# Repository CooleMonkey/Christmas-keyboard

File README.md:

# Christmas-keyboard
I will tell you something about my project. As the title already says, it's a christmas themed keyboard. I made the size 60/65% and I added a numpad to the left cause I hate it when the numpad to the right is in the way of my mouse.
So that's also the first reason why I made this project. The second reason is that I wanted to challenge myself during my holliday, instead of speningd hours and hours gaming and I definitely challenged myself.
The third reason was the fact that the best christmas themed project shipped before monday 5 januari 2026 would get a 3d-printer. That was a great motivation for me to start this project, cause I really want a 3d-printer.

During this project I had some struggles with the PCB and the 3d-case, but eventually I got everyhting the right way I wanted it, so I'm pretty happy when I'm looking back at the time I have spent into this project.
The case is made up of 5 parts so it can be printed in a 3d printer.

## PCB

## Full 3D Model

## 3D Case

## Bottom Case R

## Bottom Case L

## Top Case R

## Top Case L1

## Top Case L2

## BOM

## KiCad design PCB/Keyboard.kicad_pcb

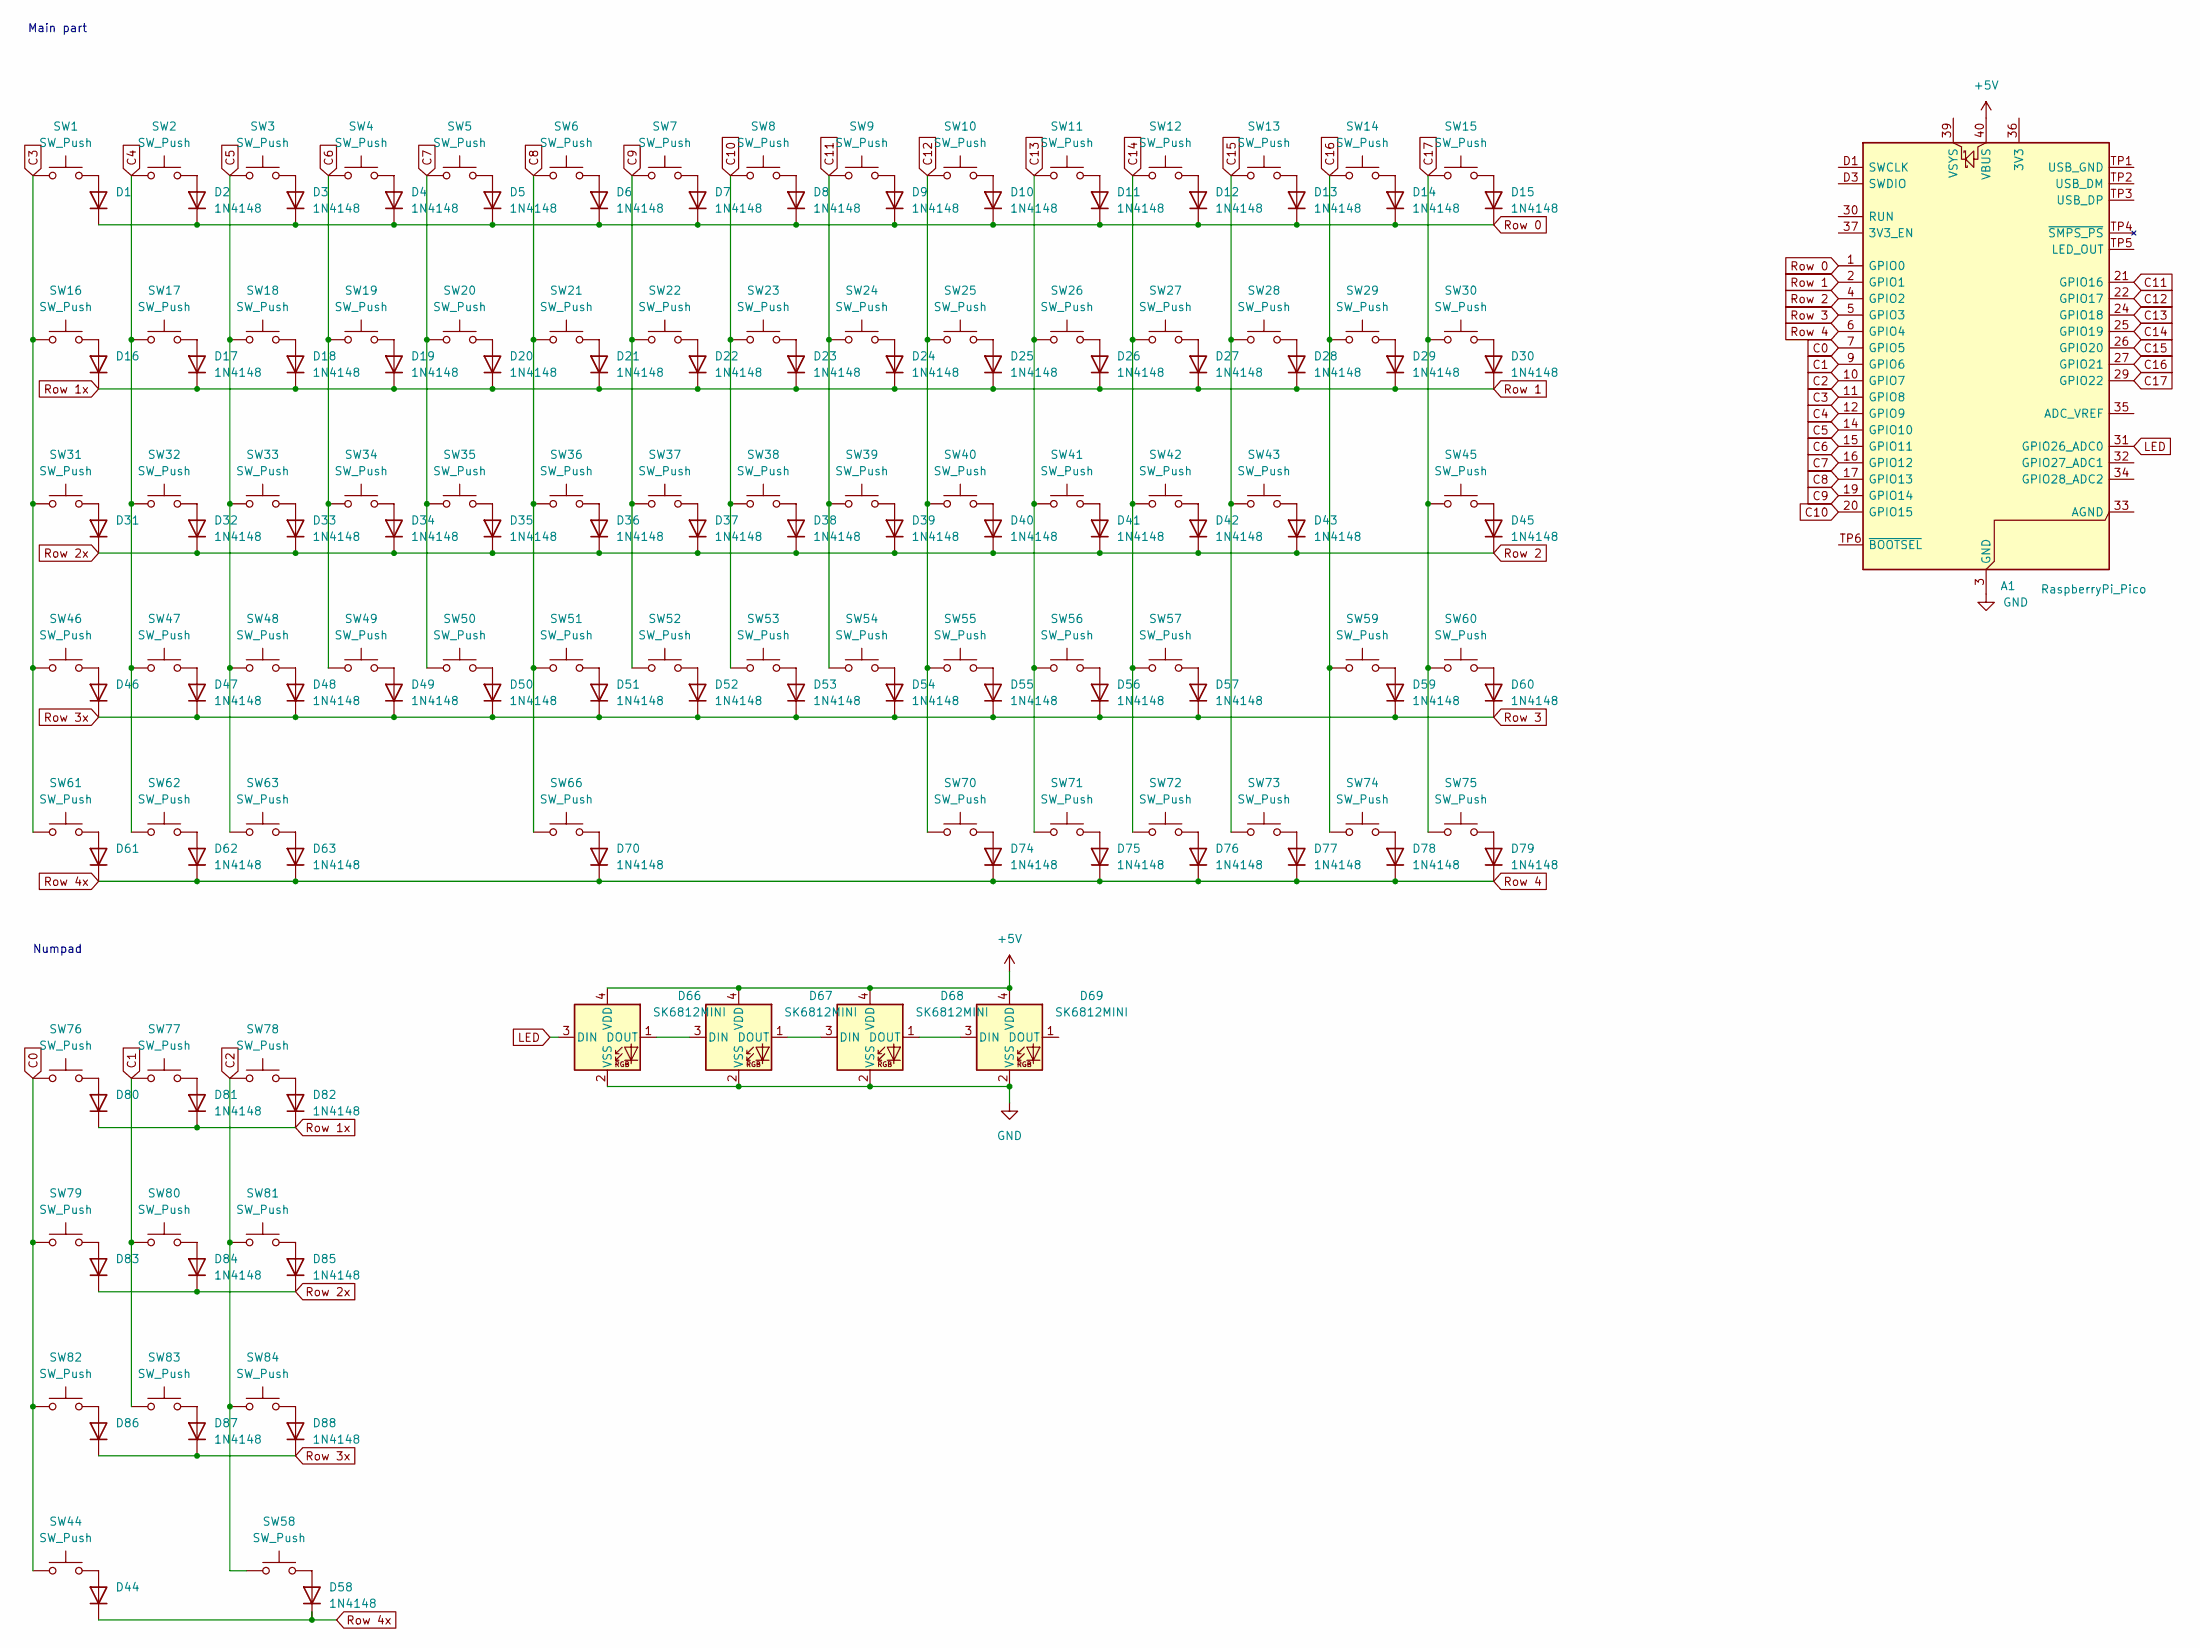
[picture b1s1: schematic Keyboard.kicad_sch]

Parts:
A1: RaspberryPi_Pico; RaspberryPi_Pico_SMD
D1, D2, D3, D4, D5, D6, D7, D8, D9, D10, D11, D12, D13, D14, D15, D16, D17, D18, D19, D20, D21, D22, D23, D24, D25, D26, D27, D28, D29, D30, D31, D32, D33, D34, D35, D36, D37, D38, D39, D40, D41, D42, D43, D44, D45, D46, D47, D48, D49, D50, D51, D52, D53, D54, D55, D56, D57, D58, D59, D60, D61, D62, D63, D70, D74, D75, D76, D77, D78, D79, D80, D81, D82, D83, D84, D85, D86, D87, D88: 1N4148; D_DO-35_SOD27_P7.62mm_Horizontal
D66, D67, D68, D69: SK6812MINI; LED_SK6812MINI_PLCC4_3.5x3.5mm_P1.75mm
SW1, SW2, SW3, SW4, SW5, SW6, SW7, SW8, SW9, SW10, SW11, SW12, SW13, SW15, SW17, SW18, SW19, SW20, SW21, SW22, SW23, SW24, SW25, SW26, SW27, SW28, SW30, SW31, SW32, SW33, SW34, SW35, SW36, SW37, SW38, SW39, SW40, SW41, SW42, SW45, SW47, SW48, SW49, SW50, SW51, SW52, SW53, SW54, SW55, SW56, SW58, SW59, SW60, SW70, SW71, SW72, SW73, SW74, SW75, SW76, SW77, SW78, SW79, SW80, SW81, SW82, SW83, SW84: SW_Push; SW_Cherry_MX_1.00u_PCB
SW14, SW44, SW46, SW57: SW_Push; SW_Cherry_MX_2.00u_PCB
SW16, SW29: SW_Push; SW_Cherry_MX_1.50u_PCB
SW43: SW_Push; SW_Cherry_MX_2.25u_PCB
SW61, SW62, SW63: SW_Push; SW_Cherry_MX_1.25u_PCB
SW66: SW_Push; SW_Cherry_MX_6.25u_PCB

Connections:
+5V: A1.40 (VBUS), D66.4 (VDD), D67.4 (VDD), D68.4 (VDD), D69.4 (VDD)
C0: A1.7 (GPIO5), SW44.1, SW76.1, SW79.1, SW82.1
C1: A1.9 (GPIO6), SW77.1, SW80.1, SW83.1
C2: A1.10 (GPIO7), SW58.1, SW78.1, SW81.1, SW84.1
C3: A1.11 (GPIO8), SW1.1, SW16.1, SW31.1, SW46.1, SW61.1
C4: A1.12 (GPIO9), SW2.1, SW17.1, SW32.1, SW47.1, SW62.1
C5: A1.14 (GPIO10), SW3.1, SW18.1, SW33.1, SW48.1, SW63.1
C6: A1.15 (GPIO11), SW4.1, SW19.1, SW34.1, SW49.1
C7: A1.16 (GPIO12), SW5.1, SW20.1, SW35.1, SW50.1
C8: A1.17 (GPIO13), SW6.1, SW21.1, SW36.1, SW51.1, SW66.1
C9: A1.19 (GPIO14), SW7.1, SW22.1, SW37.1, SW52.1
C10: A1.20 (GPIO15), SW8.1, SW23.1, SW38.1, SW53.1
C11: A1.21 (GPIO16), SW9.1, SW24.1, SW39.1, SW54.1
C12: A1.22 (GPIO17), SW10.1, SW25.1, SW40.1, SW55.1, SW70.1
C13: A1.24 (GPIO18), SW11.1, SW26.1, SW41.1, SW56.1, SW71.1
C14: A1.25 (GPIO19), SW12.1, SW27.1, SW42.1, SW57.1, SW72.1
C15: A1.26 (GPIO20), SW13.1, SW28.1, SW43.1, SW73.1
C16: A1.27 (GPIO21), SW14.1, SW29.1, SW59.1, SW74.1
C17: A1.29 (GPIO22), SW15.1, SW30.1, SW45.1, SW60.1, SW75.1
GND: A1.3 (GND), A1.8 (GND), A1.13 (GND), A1.18 (GND), A1.23 (GND), A1.28 (GND), A1.38 (GND), A1.D2 (GND), D66.2 (VSS), D67.2 (VSS), D68.2 (VSS), D69.2 (VSS)
LED: A1.31 (GPIO26_ADC0), D66.3 (DIN)
unnamed: D1.2 (A), SW1.2
unnamed: D2.2 (A), SW2.2
unnamed: D3.2 (A), SW3.2
unnamed: D4.2 (A), SW4.2
unnamed: D5.2 (A), SW5.2
unnamed: D6.2 (A), SW6.2
unnamed: D7.2 (A), SW7.2
unnamed: D8.2 (A), SW8.2
unnamed: D9.2 (A), SW9.2
unnamed: D10.2 (A), SW10.2
unnamed: D11.2 (A), SW11.2
unnamed: D12.2 (A), SW12.2
unnamed: D13.2 (A), SW13.2
unnamed: D14.2 (A), SW14.2
unnamed: D15.2 (A), SW15.2
unnamed: D16.2 (A), SW16.2
unnamed: D17.2 (A), SW17.2
unnamed: D18.2 (A), SW18.2
unnamed: D19.2 (A), SW19.2
unnamed: D20.2 (A), SW20.2
unnamed: D21.2 (A), SW21.2
unnamed: D22.2 (A), SW22.2
unnamed: D23.2 (A), SW23.2
unnamed: D24.2 (A), SW24.2
unnamed: D25.2 (A), SW25.2
unnamed: D26.2 (A), SW26.2
unnamed: D27.2 (A), SW27.2
unnamed: D28.2 (A), SW28.2
unnamed: D29.2 (A), SW29.2
unnamed: D30.2 (A), SW30.2
unnamed: D31.2 (A), SW31.2
unnamed: D32.2 (A), SW32.2
unnamed: D33.2 (A), SW33.2
unnamed: D34.2 (A), SW34.2
unnamed: D35.2 (A), SW35.2
unnamed: D36.2 (A), SW36.2
unnamed: D37.2 (A), SW37.2
unnamed: D38.2 (A), SW38.2
unnamed: D39.2 (A), SW39.2
unnamed: D40.2 (A), SW40.2
unnamed: D41.2 (A), SW41.2
unnamed: D42.2 (A), SW42.2
unnamed: D43.2 (A), SW43.2
unnamed: D44.2 (A), SW44.2
unnamed: D45.2 (A), SW45.2
unnamed: D46.2 (A), SW46.2
unnamed: D47.2 (A), SW47.2
unnamed: D48.2 (A), SW48.2
unnamed: D49.2 (A), SW49.2
unnamed: D50.2 (A), SW50.2
unnamed: D51.2 (A), SW51.2
unnamed: D52.2 (A), SW52.2
unnamed: D53.2 (A), SW53.2
unnamed: D54.2 (A), SW54.2
unnamed: D55.2 (A), SW55.2
unnamed: D56.2 (A), SW56.2
unnamed: D57.2 (A), SW57.2
unnamed: D58.2 (A), SW58.2
unnamed: D59.2 (A), SW59.2
unnamed: D60.2 (A), SW60.2
unnamed: D61.2 (A), SW61.2
unnamed: D62.2 (A), SW62.2
unnamed: D63.2 (A), SW63.2
unnamed: D66.1 (DOUT), D67.3 (DIN)
unnamed: D67.1 (DOUT), D68.3 (DIN)
unnamed: D68.1 (DOUT), D69.3 (DIN)
unnamed: D70.2 (A), SW66.2
unnamed: D74.2 (A), SW70.2
unnamed: D75.2 (A), SW71.2
unnamed: D76.2 (A), SW72.2
unnamed: D77.2 (A), SW73.2
unnamed: D78.2 (A), SW74.2
unnamed: D79.2 (A), SW75.2
unnamed: D80.2 (A), SW76.2
unnamed: D81.2 (A), SW77.2
unnamed: D82.2 (A), SW78.2
unnamed: D83.2 (A), SW79.2
unnamed: D84.2 (A), SW80.2
unnamed: D85.2 (A), SW81.2
unnamed: D86.2 (A), SW82.2
unnamed: D87.2 (A), SW83.2
unnamed: D88.2 (A), SW84.2
Row 0: A1.1 (GPIO0), D1.1 (K), D2.1 (K), D3.1 (K), D4.1 (K), D5.1 (K), D6.1 (K), D7.1 (K), D8.1 (K), D9.1 (K), D10.1 (K), D11.1 (K), D12.1 (K), D13.1 (K), D14.1 (K), D15.1 (K)
Row 1: A1.2 (GPIO1), D16.1 (K), D17.1 (K), D18.1 (K), D19.1 (K), D20.1 (K), D21.1 (K), D22.1 (K), D23.1 (K), D24.1 (K), D25.1 (K), D26.1 (K), D27.1 (K), D28.1 (K), D29.1 (K), D30.1 (K), D80.1 (K), D81.1 (K), D82.1 (K)
Row 2: A1.4 (GPIO2), D31.1 (K), D32.1 (K), D33.1 (K), D34.1 (K), D35.1 (K), D36.1 (K), D37.1 (K), D38.1 (K), D39.1 (K), D40.1 (K), D41.1 (K), D42.1 (K), D43.1 (K), D45.1 (K), D83.1 (K), D84.1 (K), D85.1 (K)
Row 3: A1.5 (GPIO3), D46.1 (K), D47.1 (K), D48.1 (K), D49.1 (K), D50.1 (K), D51.1 (K), D52.1 (K), D53.1 (K), D54.1 (K), D55.1 (K), D56.1 (K), D57.1 (K), D59.1 (K), D60.1 (K), D86.1 (K), D87.1 (K), D88.1 (K)
Row 4: A1.6 (GPIO4), D44.1 (K), D58.1 (K), D61.1 (K), D62.1 (K), D63.1 (K), D70.1 (K), D74.1 (K), D75.1 (K), D76.1 (K), D77.1 (K), D78.1 (K), D79.1 (K)

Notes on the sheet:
Numpad
Main part

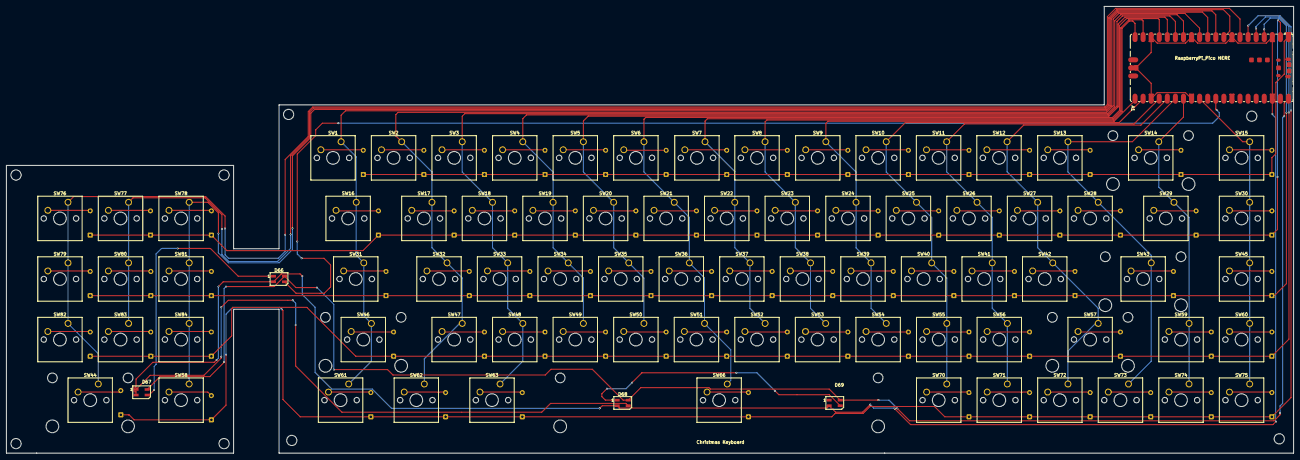
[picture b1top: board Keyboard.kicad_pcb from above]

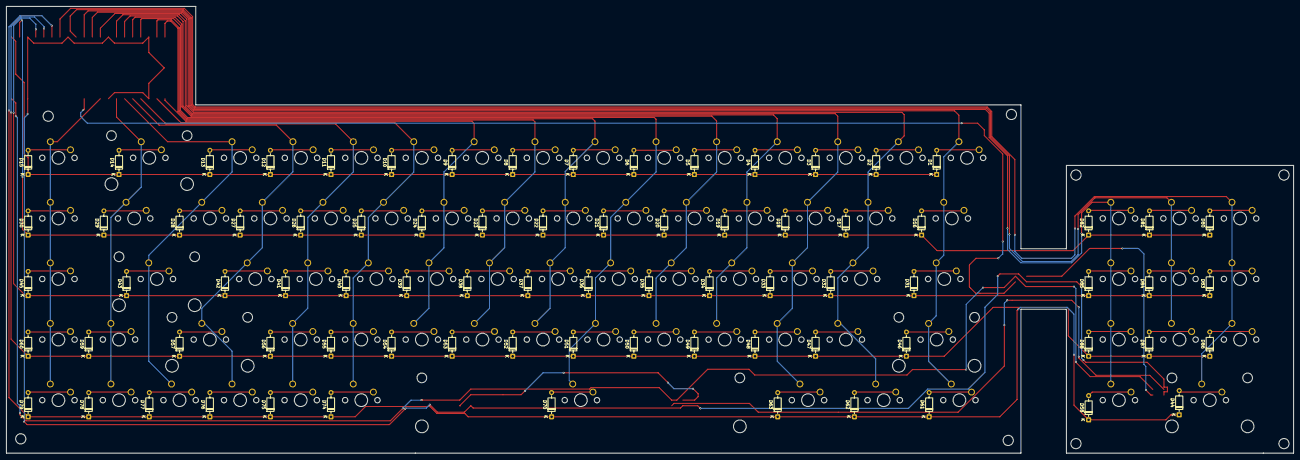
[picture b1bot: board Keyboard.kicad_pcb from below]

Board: 2 copper layers, 404.8 x 140.5 mm, 163 parts (79 on the bottom side), 108 nets.

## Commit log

2025-12-30 Add journal entry about keyboard layout design
    Documented keyboard layout design and usage plan.
2025-12-30 Enhance README with detailed project motivation
    Expanded project description to include reasons for creating a custom keyboard and layout preferences.
2025-12-31 Add entry about 3D case design considerations
    Document thoughts on 3D case design for keyboard.
2025-12-31 Document progress on right bottom case assembly
    Added an entry about the progress on the right bottom case, including challenges and considerations for securing the PCB.
2025-12-31 Revise journal entry for 31-12-2025
    Updated journal entry with time spent and future plans.
2026-01-01 Add journal entry for January 1, 2026
    Added journal entry for January 1, 2026, detailing improvements made to the PCB board and right bottom case.
2026-01-01 Add journal entries for January 1, 2026
    Added new journal entries for January 1, 2026, detailing progress on the project.
2026-01-01 Add image to journal entry on 1-1-2026
    Added an image to the journal entry for better documentation.
2026-01-01 Document progress on Upper right case in JOURNAL.md
    Added a new entry documenting progress on the Upper right case.
2026-01-01 Document progress on upper case and firmware plans
    Added entry for completion of upper case and firmware plans.
2026-01-01 Add journal entry for coding session on 1-1-2026
    Added journal entry about coding progress and challenges.
2026-01-01 Document new progress in JOURNAL.md
    Added new entry for 1-1-2026 at 23:00 with updates.
2026-01-02 Revise README with detailed project overview
    Expanded project description and motivations for creating a custom Christmas-themed keyboard, including challenges faced and goals.
2026-01-02 Update README with PCB and 3D model images
    Added images for PCB and full 3D model in README.
2026-01-02 Add BOM section with image to README
2026-01-02 Add new image to BOM section
    Added a new image to the BOM section of the README.
2026-01-02 Add new image to BOM section in README
    Added a new image for the BOM section in README.
2026-01-02 Add new BOM image to README
2026-01-13 Update BOM with new product entries
    Added new product entries and updated existing ones in the BOM.
2026-01-13 Revise BOM for Christmas themed keyboard
    Updated product details and prices in the BOM for the Christmas themed keyboard.
2026-01-13 Fix formatting and improve README content
2026-01-24 Add new images to PCB section in README
2026-01-24 Update JOURNAL with recent progress and fixes
    Added a new entry about fixing LED connections and reuploading files.
2026-01-24 Add entry about LED pin change and images
    Updated the journal with feedback on LED pin usage and added images.
2026-02-04 Enhance journal entries with project details
    Expanded journal entries with additional details about the keyboard layout project, including wiring and lighting updates.
